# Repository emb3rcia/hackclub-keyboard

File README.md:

# hackclub-keyboard
Keyboard with hot-swap and rotational knob made alongside grant program from hackclub.com

# Reasons why i made this project

I made this keyboard for few reasons:
1. I wanted to make something more complicated than hackpad
2. I like doing things
3. I need new keyboard badly as mine is randomly doubling characters or holding them down or not registering space
4. I wanted something that i made not that i bought from random seller

# CAD Pictures:
Fusion 360 screenshot of full model (except switches as it is too much of hassle to add them and they would be covered by keycaps that can vary from person to person!)

USB Port Cutout (11x6.5mm)

# PCB Pictures:
Schematics:

PCB:

PCB 3D Viewer KiCad:
Front:

Back:

# BOM:

| Item | Price USD | Link |
| --- | --- | --- |
| Keycaps | 18.11 | https://www.aliexpress.com/item/1005008465121722.html |
| Stabilizers | 9.90 | https://www.aliexpress.com/item/4001143514438.html |
| M2x4mm screws | 1.28 | https://www.aliexpress.com/item/1005008799074471.html |
| DFRobot EC11 Encoder | 3.81 + 1.37 shipping | https://botland.com.pl/enkodery/9533-czujnik-obrotu-impulsator-enkoder-obrotowy-dfrobot-ec11-6959420912414.html |
| JLCPCB PCB | 44.52 | https://www.jlcpcb.com |
| IN4148W T4 Diodes | 2.12 | https://www.aliexpress.com/item/1005009063199018.html |
| Gateron Hot-Swap Sockets (90pcs) | 7.30 | https://www.aliexpress.com/item/1005002637150446.html |
| Gateron Switches (90pcs) | 25.19 | https://www.aliexpress.com/item/1005006376024657.html |
| Raspberry Pi Pico | 3.53 | https://www.aliexpress.com/item/1005006087823796.html |
| Total | USD | - |
| - | 117.13 | - |

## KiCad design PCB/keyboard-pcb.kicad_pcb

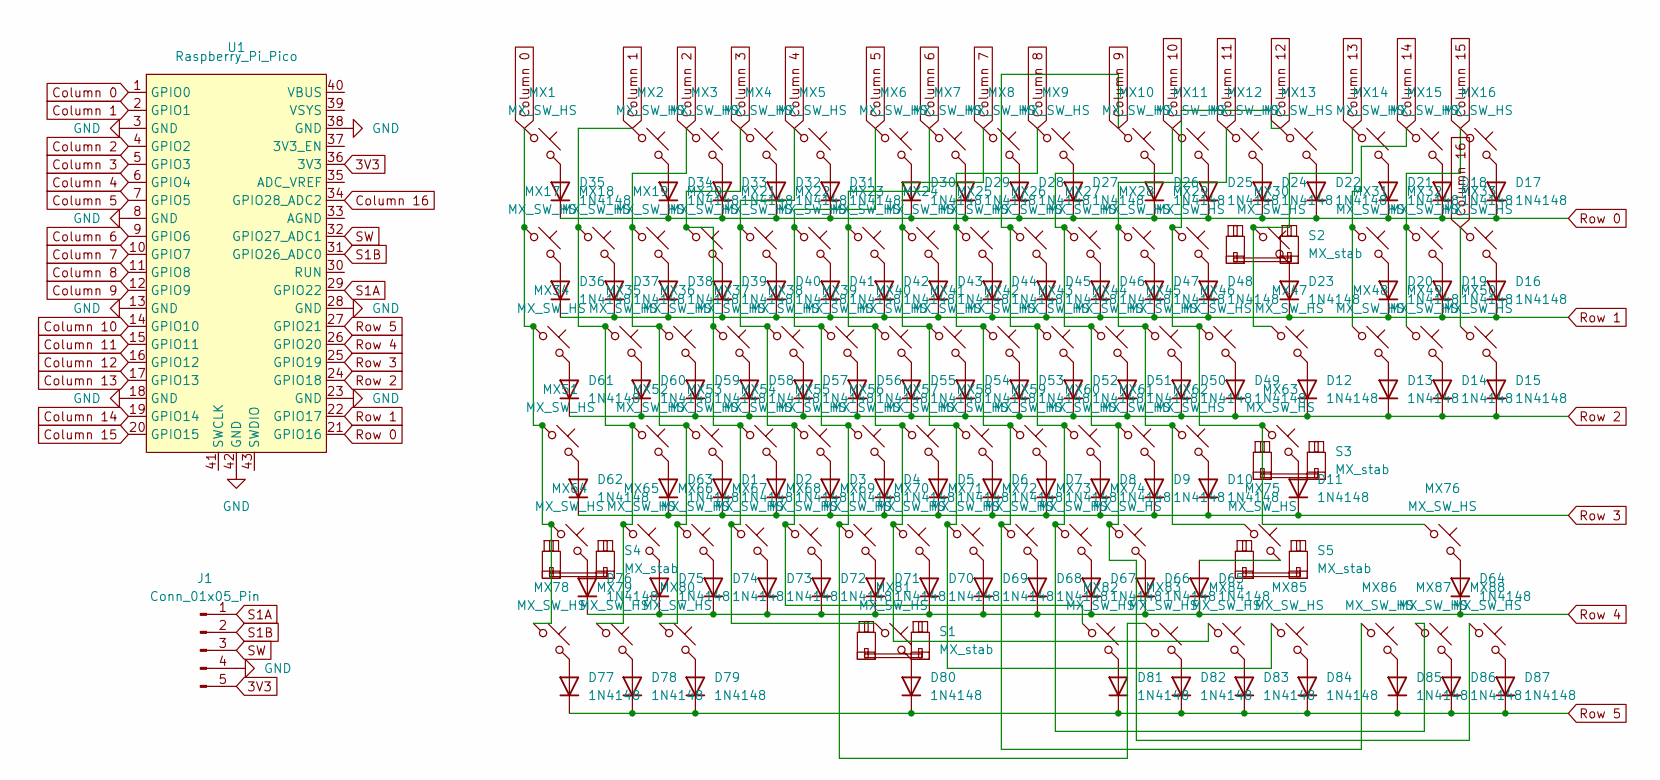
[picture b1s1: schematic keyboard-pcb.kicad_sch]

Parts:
D1, D2, D3, D4, D5, D6, D7, D8, D9, D10, D11, D12, D13, D14, D15, D16, D17, D18, D19, D20, D21, D22, D23, D24, D25, D26, D27, D28, D29, D30, D31, D32, D33, D34, D35, D36, D37, D38, D39, D40, D41, D42, D43, D44, D45, D46, D47, D48, D49, D50, D51, D52, D53, D54, D55, D56, D57, D58, D59, D60, D61, D62, D63, D64, D65, D66, D67, D68, D69, D70, D71, D72, D73, D74, D75, D76, D77, D78, D79, D80, D81, D82, D83, D84, D85, D86, D87: 1N4148; D_DO-35_SOD27_P7.62mm_Horizontal
J1: Conn_01x05_Pin; PinHeader_1x05_P2.54mm_Vertical
MX1, MX2, MX3, MX4, MX5, MX6, MX7, MX8, MX9, MX10, MX11, MX12, MX13, MX14, MX15, MX16, MX17, MX18, MX19, MX20, MX21, MX22, MX23, MX24, MX25, MX26, MX27, MX28, MX29, MX30, MX31, MX32, MX33, MX34, MX35, MX36, MX37, MX38, MX39, MX40, MX41, MX42, MX43, MX44, MX45, MX46, MX47, MX48, MX49, MX50, MX51, MX52, MX53, MX54, MX55, MX56, MX57, MX58, MX59, MX60, MX61, MX62, MX63, MX64, MX65, MX66, MX67, MX68, MX69, MX70, MX71, MX72, MX73, MX74, MX75, MX76, MX78, MX79, MX80, MX81, MX82, MX83, MX84, MX85, MX86, MX87, MX88: MX_SW_HS; SW_MX_HS_KS-2P02B01-01_1u
S1: MX_stab; STAB_MX_P_6.25u
S2: MX_stab; STAB_MX_P_2u
S3, S4: MX_stab; STAB_MX_P_2.25u
S5: MX_stab; STAB_MX_P_2.75u
U1: Raspberry_Pi_Pico

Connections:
3V3: J1.5, U1.36 (3V3)
Column 0: MX1.1, MX17.1, MX34.1, MX51.1, MX64.1, MX78.1, U1.1 (GPIO0)
Column 1: MX2.1, MX18.1, MX35.1, MX52.1, MX65.1, MX79.1, U1.2 (GPIO1)
Column 2: MX3.1, MX19.1, MX36.1, MX53.1, MX66.1, MX80.1, U1.4 (GPIO2)
Column 3: MX4.1, MX20.1, MX37.1, MX54.1, MX67.1, MX81.1, U1.5 (GPIO3)
Column 4: MX5.1, MX21.1, MX38.1, MX55.1, MX68.1, MX82.1, U1.6 (GPIO4)
Column 5: MX6.1, MX22.1, MX39.1, MX56.1, MX69.1, MX83.1, U1.7 (GPIO5)
Column 6: MX7.1, MX23.1, MX40.1, MX57.1, MX70.1, MX84.1, U1.9 (GPIO6)
Column 7: MX8.1, MX24.1, MX41.1, MX58.1, MX71.1, MX85.1, U1.10 (GPIO7)
Column 8: MX9.1, MX25.1, MX42.1, MX59.1, MX72.1, MX86.1, U1.11 (GPIO8)
Column 9: MX10.1, MX26.1, MX43.1, MX60.1, MX73.1, MX87.1, U1.12 (GPIO9)
Column 10: MX11.1, MX27.1, MX44.1, MX61.1, MX74.1, MX88.1, U1.14 (GPIO10)
Column 11: MX12.1, MX28.1, MX45.1, MX62.1, MX75.1, U1.15 (GPIO11)
Column 12: MX13.1, MX29.1, MX46.1, MX63.1, MX76.1, U1.16 (GPIO12)
Column 13: MX14.1, MX30.1, MX47.1, U1.17 (GPIO13)
Column 14: MX15.1, MX31.1, MX48.1, U1.19 (GPIO14)
Column 15: MX16.1, MX32.1, MX49.1, U1.20 (GPIO15)
Column 16: MX33.1, MX50.1, U1.34 (GPIO28_ADC2)
GND: J1.4, U1.3 (GND), U1.8 (GND), U1.13 (GND), U1.18 (GND), U1.23 (GND), U1.28 (GND), U1.38 (GND), U1.42 (GND)
unnamed: D1.2 (A), MX53.2
unnamed: D2.2 (A), MX54.2
unnamed: D3.2 (A), MX55.2
unnamed: D4.2 (A), MX56.2
unnamed: D5.2 (A), MX57.2
unnamed: D6.2 (A), MX58.2
unnamed: D7.2 (A), MX59.2
unnamed: D8.2 (A), MX60.2
unnamed: D9.2 (A), MX61.2
unnamed: D10.2 (A), MX62.2
unnamed: D11.2 (A), MX63.2
unnamed: D12.2 (A), MX47.2
unnamed: D13.2 (A), MX48.2
unnamed: D14.2 (A), MX49.2
unnamed: D15.2 (A), MX50.2
unnamed: D16.2 (A), MX33.2
unnamed: D17.2 (A), MX16.2
unnamed: D18.2 (A), MX15.2
unnamed: D19.2 (A), MX32.2
unnamed: D20.2 (A), MX31.2
unnamed: D21.2 (A), MX14.2
unnamed: D22.2 (A), MX13.2
unnamed: D23.2 (A), MX30.2
unnamed: D24.2 (A), MX12.2
unnamed: D25.2 (A), MX11.2
unnamed: D26.2 (A), MX10.2
unnamed: D27.2 (A), MX9.2
unnamed: D28.2 (A), MX8.2
unnamed: D29.2 (A), MX7.2
unnamed: D30.2 (A), MX6.2
unnamed: D31.2 (A), MX5.2
unnamed: D32.2 (A), MX4.2
unnamed: D33.2 (A), MX3.2
unnamed: D34.2 (A), MX2.2
unnamed: D35.2 (A), MX1.2
unnamed: D36.2 (A), MX17.2
unnamed: D37.2 (A), MX18.2
unnamed: D38.2 (A), MX19.2
unnamed: D39.2 (A), MX20.2
unnamed: D40.2 (A), MX21.2
unnamed: D41.2 (A), MX22.2
unnamed: D42.2 (A), MX23.2
unnamed: D43.2 (A), MX24.2
unnamed: D44.2 (A), MX25.2
unnamed: D45.2 (A), MX26.2
unnamed: D46.2 (A), MX27.2
unnamed: D47.2 (A), MX28.2
unnamed: D48.2 (A), MX29.2
unnamed: D49.2 (A), MX46.2
unnamed: D50.2 (A), MX45.2
unnamed: D51.2 (A), MX44.2
unnamed: D52.2 (A), MX43.2
unnamed: D53.2 (A), MX42.2
unnamed: D54.2 (A), MX41.2
unnamed: D55.2 (A), MX40.2
unnamed: D56.2 (A), MX39.2
unnamed: D57.2 (A), MX38.2
unnamed: D58.2 (A), MX37.2
unnamed: D59.2 (A), MX36.2
unnamed: D60.2 (A), MX35.2
unnamed: D61.2 (A), MX34.2
unnamed: D62.2 (A), MX51.2
unnamed: D63.2 (A), MX52.2
unnamed: D64.2 (A), MX76.2
unnamed: D65.2 (A), MX75.2
unnamed: D66.2 (A), MX74.2
unnamed: D67.2 (A), MX73.2
unnamed: D68.2 (A), MX72.2
unnamed: D69.2 (A), MX71.2
unnamed: D70.2 (A), MX70.2
unnamed: D71.2 (A), MX69.2
unnamed: D72.2 (A), MX68.2
unnamed: D73.2 (A), MX67.2
unnamed: D74.2 (A), MX66.2
unnamed: D75.2 (A), MX65.2
unnamed: D76.2 (A), MX64.2
unnamed: D77.2 (A), MX78.2
unnamed: D78.2 (A), MX79.2
unnamed: D79.2 (A), MX80.2
unnamed: D80.2 (A), MX81.2
unnamed: D81.2 (A), MX82.2
unnamed: D82.2 (A), MX83.2
unnamed: D83.2 (A), MX84.2
unnamed: D84.2 (A), MX85.2
unnamed: D85.2 (A), MX86.2
unnamed: D86.2 (A), MX87.2
unnamed: D87.2 (A), MX88.2
Row 0: D17.1 (K), D18.1 (K), D21.1 (K), D22.1 (K), D24.1 (K), D25.1 (K), D26.1 (K), D27.1 (K), D28.1 (K), D29.1 (K), D30.1 (K), D31.1 (K), D32.1 (K), D33.1 (K), D34.1 (K), D35.1 (K), U1.21 (GPIO16)
Row 1: D16.1 (K), D19.1 (K), D20.1 (K), D23.1 (K), D36.1 (K), D37.1 (K), D38.1 (K), D39.1 (K), D40.1 (K), D41.1 (K), D42.1 (K), D43.1 (K), D44.1 (K), D45.1 (K), D46.1 (K), D47.1 (K), D48.1 (K), U1.22 (GPIO17)
Row 2: D12.1 (K), D13.1 (K), D14.1 (K), D15.1 (K), D49.1 (K), D50.1 (K), D51.1 (K), D52.1 (K), D53.1 (K), D54.1 (K), D55.1 (K), D56.1 (K), D57.1 (K), D58.1 (K), D59.1 (K), D60.1 (K), D61.1 (K), U1.24 (GPIO18)
Row 3: D1.1 (K), D2.1 (K), D3.1 (K), D4.1 (K), D5.1 (K), D6.1 (K), D7.1 (K), D8.1 (K), D9.1 (K), D10.1 (K), D11.1 (K), D62.1 (K), D63.1 (K), U1.25 (GPIO19)
Row 4: D64.1 (K), D65.1 (K), D66.1 (K), D67.1 (K), D68.1 (K), D69.1 (K), D70.1 (K), D71.1 (K), D72.1 (K), D73.1 (K), D74.1 (K), D75.1 (K), D76.1 (K), U1.26 (GPIO20)
Row 5: D77.1 (K), D78.1 (K), D79.1 (K), D80.1 (K), D81.1 (K), D82.1 (K), D83.1 (K), D84.1 (K), D85.1 (K), D86.1 (K), D87.1 (K), U1.27 (GPIO21)
S1A: J1.1, U1.29 (GPIO22)
S1B: J1.2, U1.31 (GPIO26_ADC0)
SW: J1.3, U1.32 (GPIO27_ADC1)

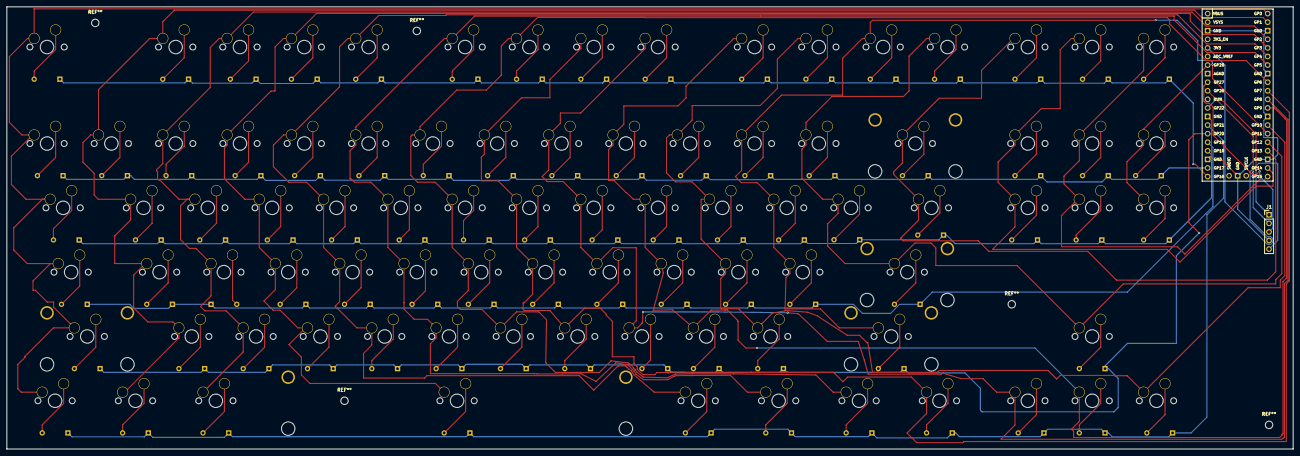
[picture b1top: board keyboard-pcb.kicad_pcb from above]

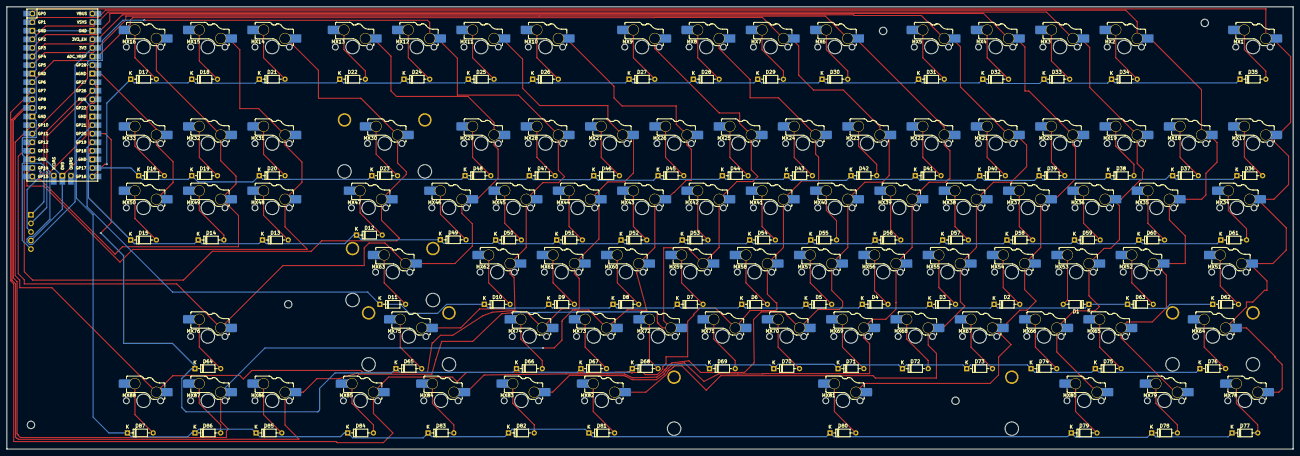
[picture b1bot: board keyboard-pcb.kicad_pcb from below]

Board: 2 copper layers, 381.0 x 131.0 mm, 181 parts (175 on the bottom side), 115 nets.

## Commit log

2025-07-17 Added JOURNAL.md
2025-07-17 Updated JOURNAL.md
2025-07-18 Modified JOUNRNAL.md - added new entry; Added /assets/ folder for images
2025-07-18 Modified JOUNRNAL.md
2025-07-19 Modified JOURNAL.md: Addded new entry
2025-07-19 Modified JOURNAL.md
2025-07-20 Modified JOUNRNAL.md; Added images to /assets/
2025-07-20 Modified JOUNRNAL.md - Fixed formatting a bit
2025-07-20 Modified JOURNAL.md and README.md; Added BOM.csv
2025-07-20 Modified README.md
2025-07-20 Fixed PCB; Added /firmware/
2025-07-31 Modified whole case, added accents (jinx from arcane reference), connected all gnd pins
2025-07-31 Fixed schem imahe in readme
2025-08-01 added missing cad file
2025-08-09 changed image in readme to correct one
2025-08-16 Fixed things ig
2025-08-16 fixed stuff ig
2025-08-16 fixed readme
2025-09-12 Adjusted prices
    Updated BOM to reflect new pricing and removed PLN column.
